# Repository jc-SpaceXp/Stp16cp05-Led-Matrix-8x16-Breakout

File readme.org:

* STP16CP05 LED Matrix 8x16 Breakout (0805 Metric)
Note: All components have the correct name/part-number however the description and datasheet will be incorrect (if names were changed)
** Schematic
[[file:stp16cp05_led_matrix_8x16_breakout/schematic_v04.pdf]]
** BOM
[[file:stp16cp05_led_matrix_8x16_breakout/stp16cp05_led_matrix_8x16_breakout_m0805_bom.csv]]
** 3D PCB Models
[[file:stp16cp05_led_matrix_8x16_breakout/pcb_3d_front.png]]
[[file:stp16cp05_led_matrix_8x16_breakout/pcb_3d_back.png]]

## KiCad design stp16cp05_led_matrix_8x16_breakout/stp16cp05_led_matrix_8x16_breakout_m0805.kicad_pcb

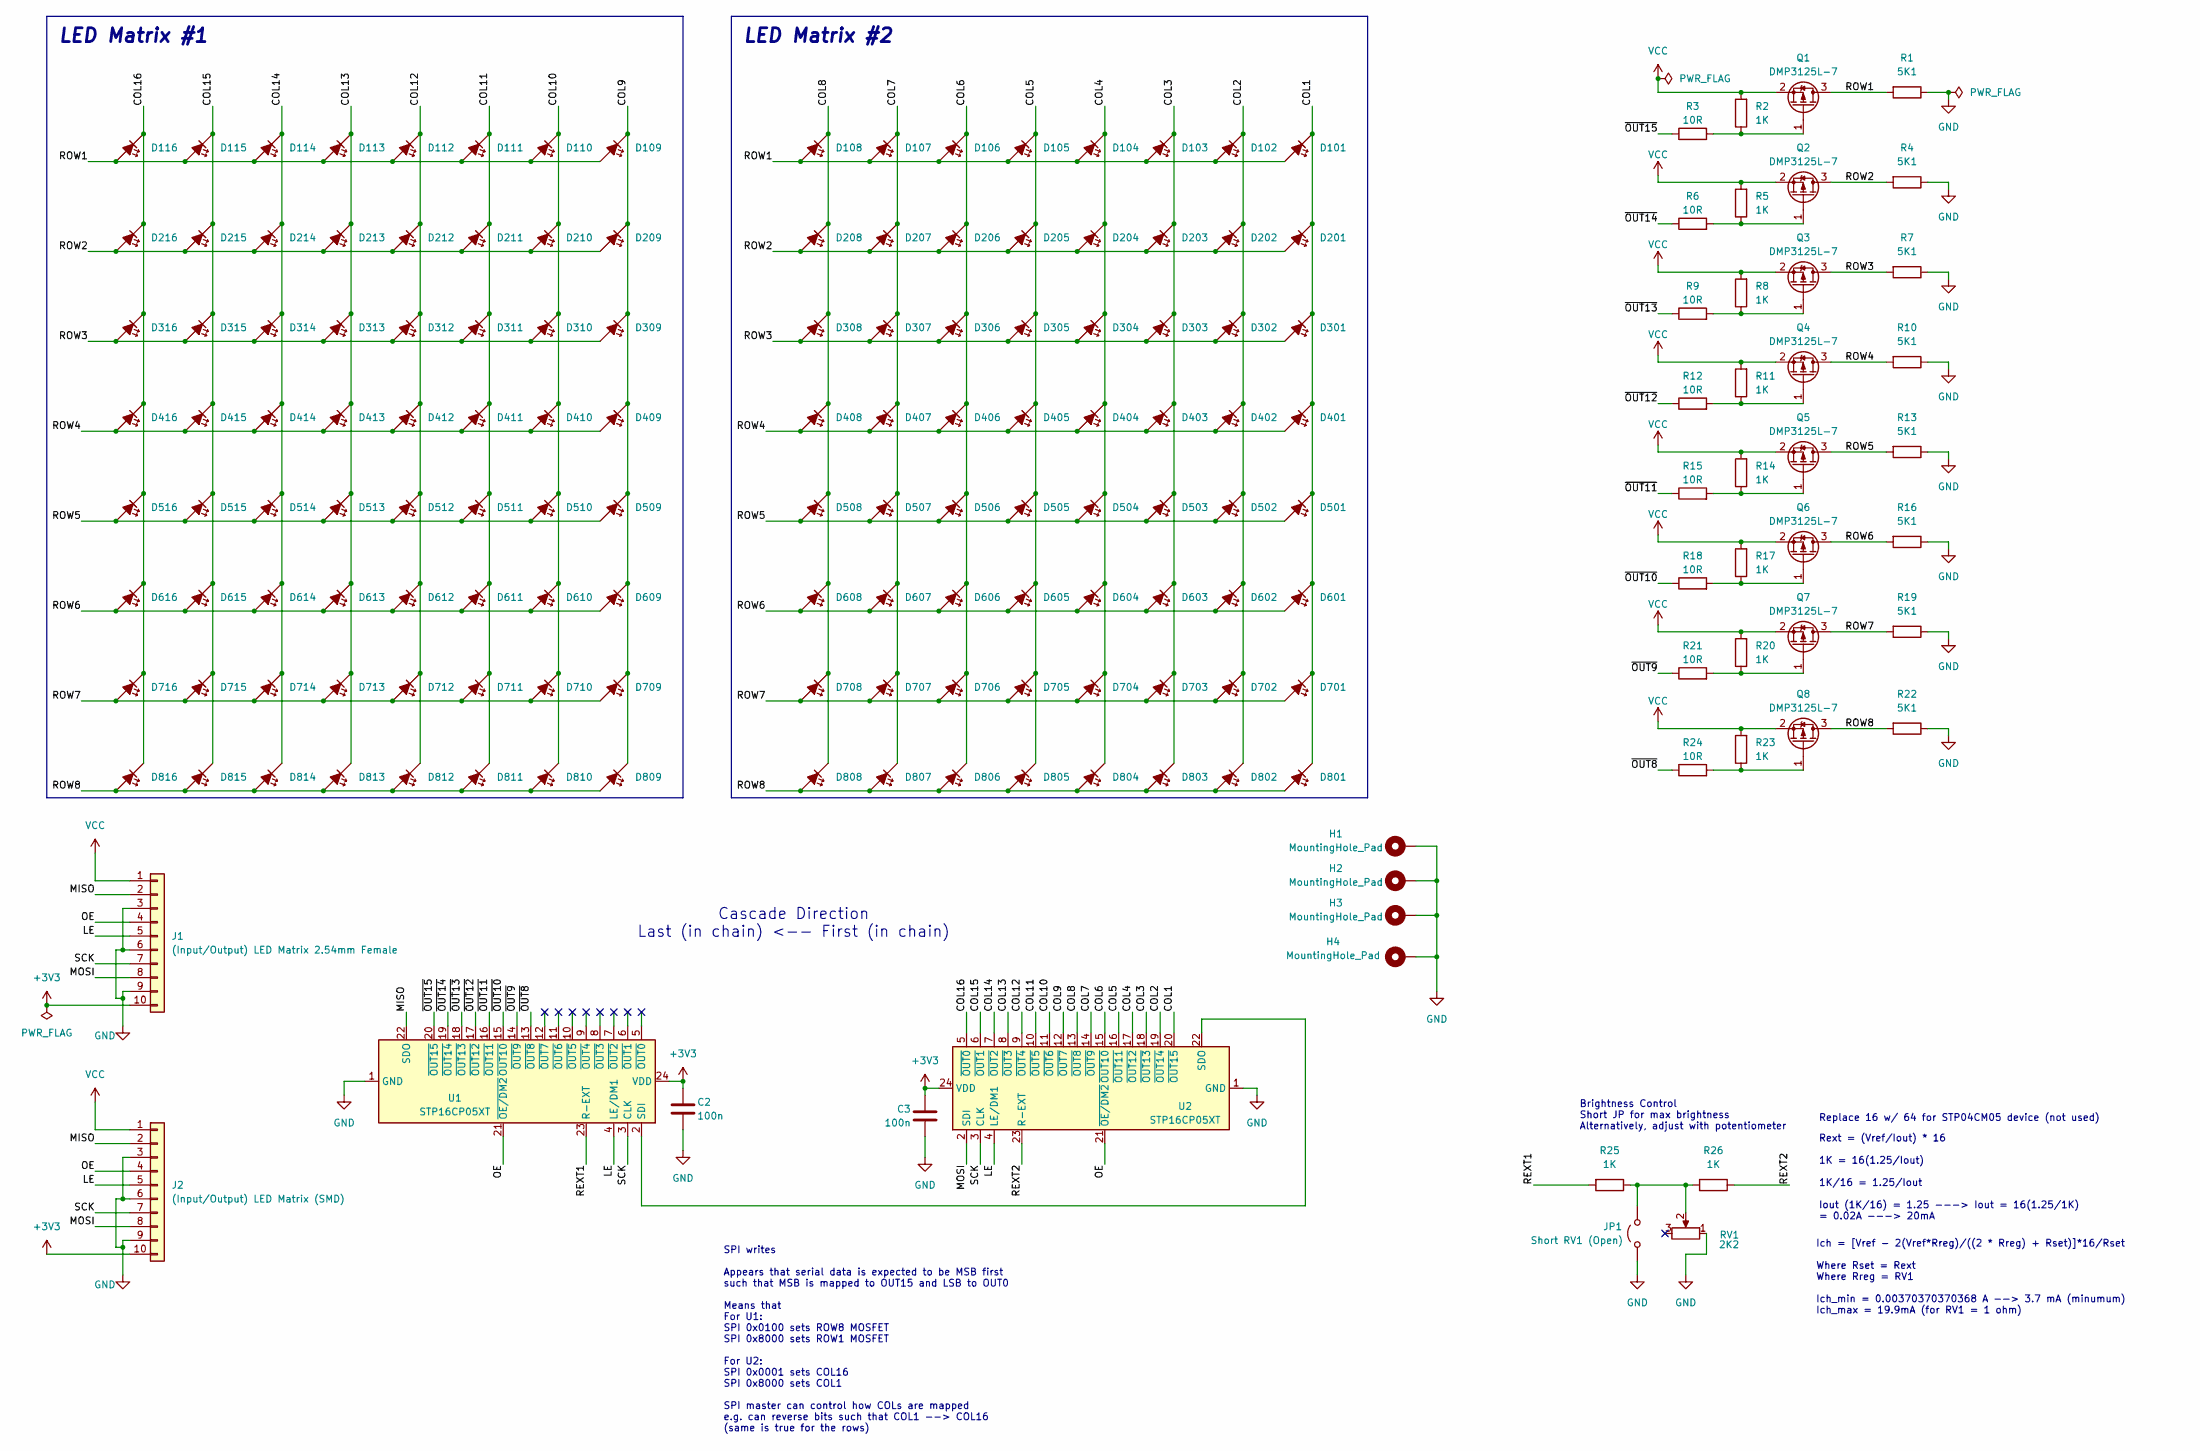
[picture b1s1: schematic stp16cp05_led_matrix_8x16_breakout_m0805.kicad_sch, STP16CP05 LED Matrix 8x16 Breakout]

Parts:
C2, C3: 100n; C_0603_1608Metric
D101, D102, D103, D104, D105, D106, D107, D108, D109, D110, D111, D112, D113, D114, D115, D116, D201, D202, D203, D204, D205, D206, D207, D208, D209, D210, D211, D212, D213, D214, D215, D216, D301, D302, D303, D304, D305, D306, D307, D308, D309, D310, D311, D312, D313, D314, D315, D316, D401, D402, D403, D404, D405, D406, D407, D408, D409, D410, D411, D412, D413, D414, D415, D416, D501, D502, D503, D504, D505, D506, D507, D508, D509, D510, D511, D512, D513, D514, D515, D516, D601, D602, D603, D604, D605, D606, D607, D608, D609, D610, D611, D612, D613, D614, D615, D616, D701, D702, D703, D704, D705, D706, D707, D708, D709, D710, D711, D712, D713, D714, D715, D716, D801, D802, D803, D804, D805, D806, D807, D808, D809, D810, D811, D812, D813, D814, D815, D816: LTST-C171KRKT; LED_0603_1608Metric_Pad1.05x0.95mm_HandSolder
H1, H2, H3, H4: MountingHole_Pad; MountingHole_3.2mm_M3_Pad
J1: (Input/Output) LED Matrix 2.54mm Female; PinHeader_1x10_P2.54mm_Vertical
J2: (Input/Output) LED Matrix (SMD); PinHeader_1x10_P2.54mm_Vertical_SMD_Pin1Left
JP1: Short RV1 (Open); PinHeader_1x02_P2.54mm_Vertical
Q1, Q2, Q3, Q4, Q5, Q6, Q7, Q8: DMP3125L-7; SOT-23
R1, R4, R7, R10, R13, R16, R19, R22: 5K1; R_0603_1608Metric
R2, R5, R8, R11, R14, R17, R20, R23, R25, R26: 1K; R_0603_1608Metric
R3, R6, R9, R12, R15, R18, R21, R24: 10R; R_0603_1608Metric
RV1: 2K2; Potentiometer_Bourns_3386F_Vertical
U1, U2: STP16CP05XT; HTSSOP-24-1EP_4.4x7.8mm_P0.65mm_EP3.2x5mm

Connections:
+3V3: C2.1, C3.1, J1.10, J2.10, U1.24 (VDD), U2.24 (VDD)
/COL1: D101.1 (K), D201.1 (K), D301.1 (K), D401.1 (K), D501.1 (K), D601.1 (K), D701.1 (K), D801.1 (K), U2.20 (~OUT15)
/COL2: D102.1 (K), D202.1 (K), D302.1 (K), D402.1 (K), D502.1 (K), D602.1 (K), D702.1 (K), D802.1 (K), U2.19 (~OUT14)
/COL3: D103.1 (K), D203.1 (K), D303.1 (K), D403.1 (K), D503.1 (K), D603.1 (K), D703.1 (K), D803.1 (K), U2.18 (~OUT13)
/COL4: D104.1 (K), D204.1 (K), D304.1 (K), D404.1 (K), D504.1 (K), D604.1 (K), D704.1 (K), D804.1 (K), U2.17 (~OUT12)
/COL5: D105.1 (K), D205.1 (K), D305.1 (K), D405.1 (K), D505.1 (K), D605.1 (K), D705.1 (K), D805.1 (K), U2.16 (~OUT11)
/COL6: D106.1 (K), D206.1 (K), D306.1 (K), D406.1 (K), D506.1 (K), D606.1 (K), D706.1 (K), D806.1 (K), U2.15 (~OUT10)
/COL7: D107.1 (K), D207.1 (K), D307.1 (K), D407.1 (K), D507.1 (K), D607.1 (K), D707.1 (K), D807.1 (K), U2.14 (~OUT9)
/COL8: D108.1 (K), D208.1 (K), D308.1 (K), D408.1 (K), D508.1 (K), D608.1 (K), D708.1 (K), D808.1 (K), U2.13 (~OUT8)
/COL9: D109.1 (K), D209.1 (K), D309.1 (K), D409.1 (K), D509.1 (K), D609.1 (K), D709.1 (K), D809.1 (K), U2.12 (~OUT7)
/COL10: D110.1 (K), D210.1 (K), D310.1 (K), D410.1 (K), D510.1 (K), D610.1 (K), D710.1 (K), D810.1 (K), U2.11 (~OUT6)
/COL11: D111.1 (K), D211.1 (K), D311.1 (K), D411.1 (K), D511.1 (K), D611.1 (K), D711.1 (K), D811.1 (K), U2.10 (~OUT5)
/COL12: D112.1 (K), D212.1 (K), D312.1 (K), D412.1 (K), D512.1 (K), D612.1 (K), D712.1 (K), D812.1 (K), U2.9 (~OUT4)
/COL13: D113.1 (K), D213.1 (K), D313.1 (K), D413.1 (K), D513.1 (K), D613.1 (K), D713.1 (K), D813.1 (K), U2.8 (~OUT3)
/COL14: D114.1 (K), D214.1 (K), D314.1 (K), D414.1 (K), D514.1 (K), D614.1 (K), D714.1 (K), D814.1 (K), U2.7 (~OUT2)
/COL15: D115.1 (K), D215.1 (K), D315.1 (K), D415.1 (K), D515.1 (K), D615.1 (K), D715.1 (K), D815.1 (K), U2.6 (~OUT1)
/COL16: D116.1 (K), D216.1 (K), D316.1 (K), D416.1 (K), D516.1 (K), D616.1 (K), D716.1 (K), D816.1 (K), U2.5 (~OUT0)
/LE: J1.5, J2.5, U1.4 (LE/DM1), U2.4 (LE/DM1)
/MISO: J1.2, J2.2, U1.22 (SDO)
/MOSI: J1.8, J2.8, U2.2 (SDI)
/OE: J1.4, J2.4, U1.21 (~OE/DM2), U2.21 (~OE/DM2)
/REXT1: R25.2, U1.23 (R-EXT)
/REXT2: R26.1, U2.23 (R-EXT)
/ROW1: D101.2 (A), D102.2 (A), D103.2 (A), D104.2 (A), D105.2 (A), D106.2 (A), D107.2 (A), D108.2 (A), D109.2 (A), D110.2 (A), D111.2 (A), D112.2 (A), D113.2 (A), D114.2 (A), D115.2 (A), D116.2 (A), Q1.3 (D), R1.2
/ROW2: D201.2 (A), D202.2 (A), D203.2 (A), D204.2 (A), D205.2 (A), D206.2 (A), D207.2 (A), D208.2 (A), D209.2 (A), D210.2 (A), D211.2 (A), D212.2 (A), D213.2 (A), D214.2 (A), D215.2 (A), D216.2 (A), Q2.3 (D), R4.2
/ROW3: D301.2 (A), D302.2 (A), D303.2 (A), D304.2 (A), D305.2 (A), D306.2 (A), D307.2 (A), D308.2 (A), D309.2 (A), D310.2 (A), D311.2 (A), D312.2 (A), D313.2 (A), D314.2 (A), D315.2 (A), D316.2 (A), Q3.3 (D), R7.2
/ROW4: D401.2 (A), D402.2 (A), D403.2 (A), D404.2 (A), D405.2 (A), D406.2 (A), D407.2 (A), D408.2 (A), D409.2 (A), D410.2 (A), D411.2 (A), D412.2 (A), D413.2 (A), D414.2 (A), D415.2 (A), D416.2 (A), Q4.3 (D), R10.2
/ROW5: D501.2 (A), D502.2 (A), D503.2 (A), D504.2 (A), D505.2 (A), D506.2 (A), D507.2 (A), D508.2 (A), D509.2 (A), D510.2 (A), D511.2 (A), D512.2 (A), D513.2 (A), D514.2 (A), D515.2 (A), D516.2 (A), Q5.3 (D), R13.2
/ROW6: D601.2 (A), D602.2 (A), D603.2 (A), D604.2 (A), D605.2 (A), D606.2 (A), D607.2 (A), D608.2 (A), D609.2 (A), D610.2 (A), D611.2 (A), D612.2 (A), D613.2 (A), D614.2 (A), D615.2 (A), D616.2 (A), Q6.3 (D), R16.2
/ROW7: D701.2 (A), D702.2 (A), D703.2 (A), D704.2 (A), D705.2 (A), D706.2 (A), D707.2 (A), D708.2 (A), D709.2 (A), D710.2 (A), D711.2 (A), D712.2 (A), D713.2 (A), D714.2 (A), D715.2 (A), D716.2 (A), Q7.3 (D), R19.2
/ROW8: D801.2 (A), D802.2 (A), D803.2 (A), D804.2 (A), D805.2 (A), D806.2 (A), D807.2 (A), D808.2 (A), D809.2 (A), D810.2 (A), D811.2 (A), D812.2 (A), D813.2 (A), D814.2 (A), D815.2 (A), D816.2 (A), Q8.3 (D), R22.2
/SCK: J1.7, J2.7, U1.3 (CLK), U2.3 (CLK)
/~OUT8: R24.1, U1.13 (~OUT8)
/~OUT9: R21.1, U1.14 (~OUT9)
/~OUT10: R18.1, U1.15 (~OUT10)
/~OUT11: R15.1, U1.16 (~OUT11)
/~OUT12: R12.1, U1.17 (~OUT12)
/~OUT13: R9.1, U1.18 (~OUT13)
/~OUT14: R6.1, U1.19 (~OUT14)
/~OUT15: R3.1, U1.20 (~OUT15)
GND: C2.2, C3.2, H1.1, H2.1, H3.1, H4.1, J1.3, J1.6, J1.9, J2.3, J2.6, J2.9, JP1.1 (A), R1.1, R4.1, R7.1, R10.1, R13.1, R16.1, R19.1, R22.1, RV1.1, U1.1 (GND), U1.25 (GND), U2.1 (GND), U2.25 (GND)
unnamed: JP1.2 (B), R25.1, R26.2, RV1.2
unnamed: Q1.1 (G), R2.1, R3.2
unnamed: Q2.1 (G), R5.1, R6.2
unnamed: Q3.1 (G), R8.1, R9.2
unnamed: Q4.1 (G), R11.1, R12.2
unnamed: Q5.1 (G), R14.1, R15.2
unnamed: Q6.1 (G), R17.1, R18.2
unnamed: Q7.1 (G), R20.1, R21.2
unnamed: Q8.1 (G), R23.1, R24.2
unnamed: U1.2 (SDI), U2.22 (SDO)
VCC: J1.1, J2.1, Q1.2 (S), Q2.2 (S), Q3.2 (S), Q4.2 (S), Q5.2 (S), Q6.2 (S), Q7.2 (S), Q8.2 (S), R2.2, R5.2, R8.2, R11.2, R14.2, R17.2, R20.2, R23.2

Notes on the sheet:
LED Matrix #1
LED Matrix #2
Cascade Direction Last (in chain) <-- First (in chain)
Rext = (Vref/Iout) * 16 1K = 16(1.25/Iout) 1K/16 = 1.25/Iout Iout (1K/16) = 1.25 ---> Iout = 16(1.25/1K) = 0.02A ---> 20mA
Ich = [Vref - 2(Vref*Rreg)/((2 * Rreg) + Rset)]*16/Rset Where Rset = Rext Where Rreg = RV1 Ich_min = 0.00370370370368 A --> 3.7 mA (minumum) Ich_max = 19.9mA (for RV1 = 1 ohm)
Replace 16 w/ 64 for STP04CM05 device (not used)
SPI writes Appears that serial data is expected to be MSB first such that MSB is mapped to OUT15 and LSB to OUT0 Means that For U1: SPI 0x0100 sets ROW8 MOSFET SPI 0x8000 sets ROW1 MOSFET For U2: SPI 0x0001 sets COL16 SPI 0x8000 sets COL1 SPI master can control how COLs are mapped e.g. can reverse 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
Brightness Control Short JP for max brightness Alternatively, adjust with potentiometer

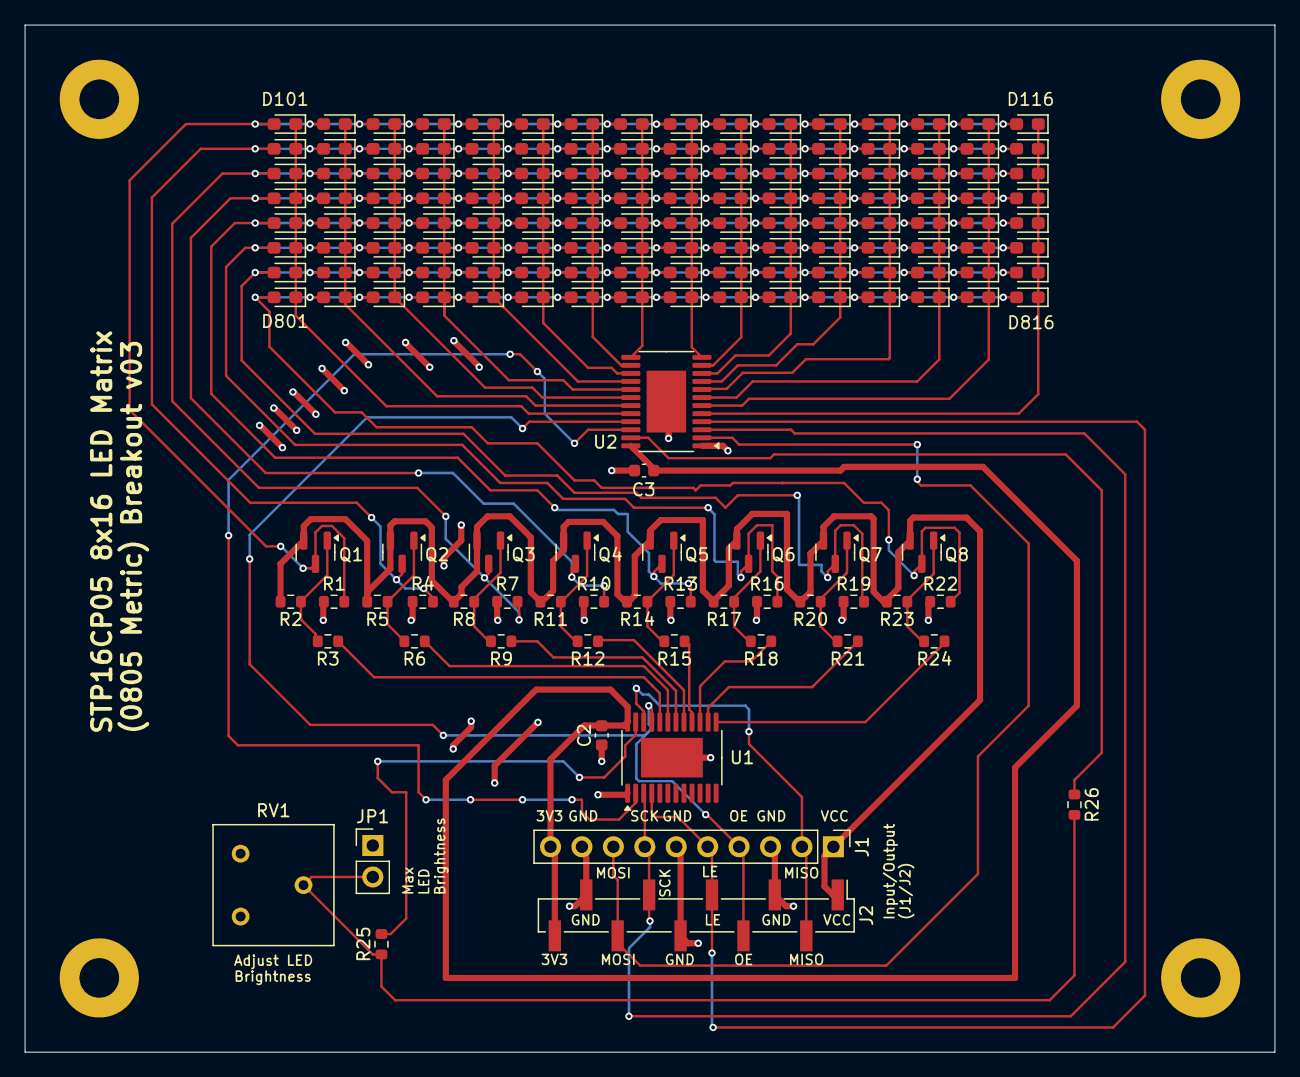
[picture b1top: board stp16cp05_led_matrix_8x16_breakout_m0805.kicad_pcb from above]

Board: 2 copper layers, 101.0 x 83.0 mm, 174 parts (0 on the bottom side), 52 nets.

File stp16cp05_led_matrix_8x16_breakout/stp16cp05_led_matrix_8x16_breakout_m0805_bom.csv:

Manufacturer Part No,Reference,Value,Qty,Footprint
C0603C104J3RACTU,"C2,C3",100n,2,Capacitor_SMD:C_0603_1608Metric
LTST-C171KRKT,"D101-D116,D201-D216,D301-D316,D401-D416,D501-D516,D601-D616,D701-D716,D801-D816",LTST-C171KRKT,128,LED_SMD:LED_0603_1608Metric_Pad1.05x0.95mm_HandSolder
77311-101-10LF,J1,(Input/Output) LED Matrix 2.54mm Female,1,Connector_PinHeader_2.54mm:PinHeader_1x10_P2.54mm_Vertical
AKSCT/G BLACK,JP1,Short RV1 (Open),1,Connector_PinHeader_2.54mm:PinHeader_1x02_P2.54mm_Vertical
DMP3125L-7,"Q1,Q2,Q3,Q4,Q5,Q6,Q7,Q8",DMP3125L-7,8,Package_TO_SOT_SMD:SOT-23
RT0603FRE075K1L,"R1,R4,R7,R10,R13,R16,R19,R22",5K1,8,Resistor_SMD:R_0603_1608Metric
RT0603DRE071KL,"R2,R5,R8,R11,R14,R17,R20,R23,R25,R26",1K,10,Resistor_SMD:R_0603_1608Metric
RT0603FRE0710RL,"R3,R6,R9,R12,R15,R18,R21,R24",10R,8,Resistor_SMD:R_0603_1608Metric
3386F-1-222LF,RV1,2K2,1,Potentiometer_THT:Potentiometer_Bourns_3386F_Vertical
STP16CP05XTTR ,"U1,U2",STP16CP05XT,2,Package_SO:HTSSOP-24-1EP_4.4x7.8mm_P0.65mm_EP3.2x5mm

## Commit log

2024-11-18 Add .gitignore
2024-11-18 Add kicad project files
    - Initial PCB version has D101 as the top right LED
2024-11-18 Updated pcb
    - D101 is now the most bottom left, going x01 to x116 from left to right
    and 1xx to 8xx going from bottom to top
2024-11-18 Add schematic (pdf)
2024-11-18 Update gitignore
2024-11-18 Update schematic
    - Use 3V3 net name over 3.3V (decimal point is hard to see in PDF)
2024-11-18 Update pcb (shcematic changes)
    - Pull in changes to schematic
2024-11-18 Add readme
2024-11-25 Update 3d models in pcb
2024-11-25 Add 3d render images
2024-11-25 Add gerber options
2024-11-25 Add gerber files
    - Settings matching OSH Park fab house
2024-11-25 Add 3d pics (png)
    - Testing if png is better than jpg on GitHub
2024-11-25 Remove jpegs
    - PNGs load better, silkscreen is much clearer
2024-11-25 Add gerber plots settings to kicad project file
2024-11-25 Add comments for schematic
    - Added helpful comments for expected SPI writes and how this effects
    which ROW/COL turns on
    - Ideally LED ROWs should be inverted on PCB to minimise signals
    crossing between layers
2024-11-26 Update pcb (flip led rows)
    - Flipped LED rows to stop the crossing tracks between layers
    - Updated gerbers and images too
2024-11-26 Update kicad file
2024-11-26 Add 3d renders to readme
2024-11-26 Add pcb revision number and text (to front silkscreen)
2024-11-26 Update 3d render and gerbers
2025-01-06 Add manufacturer part numbers to schematic symbols
2025-01-06 Add setting for BOM output file
    - Tweaked other settings to hide DNP fields and datasheet fields too
    from symbol lists
2025-01-06 Add bom csv file
2025-01-06 Update readme to include bom
2025-01-06 Exclude smd footprint from bom
    - Just some SMD pads which don't require a part
